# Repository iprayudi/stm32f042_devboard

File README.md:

# stm32f042_devboard

Use STM32CUBEIDE to run the example codes in this repository

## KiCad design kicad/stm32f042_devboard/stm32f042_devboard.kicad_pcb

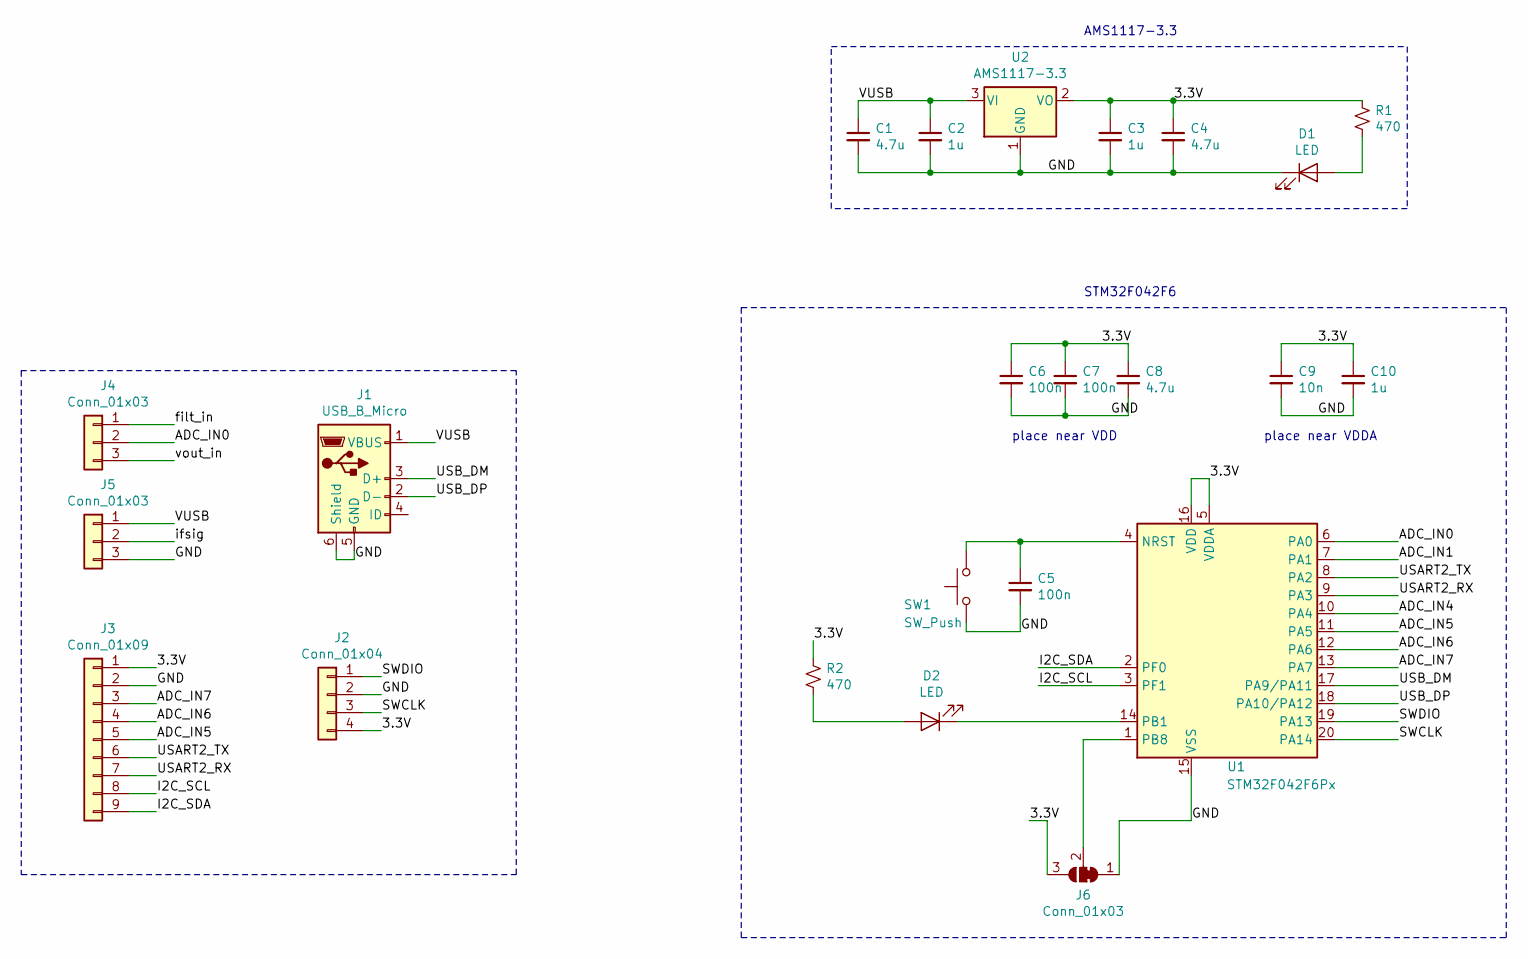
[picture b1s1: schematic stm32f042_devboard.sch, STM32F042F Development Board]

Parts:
C1, C4, C8: 4.7u; C_0805_2012Metric_Pad1.15x1.40mm_HandSolder; LCSC C1779
C2, C3, C10: 1u; C_0805_2012Metric_Pad1.15x1.40mm_HandSolder; LCSC C28323
C5, C6, C7: 100n; C_0805_2012Metric_Pad1.15x1.40mm_HandSolder; LCSC C49678
C9: 10n; C_0805_2012Metric_Pad1.15x1.40mm_HandSolder; LCSC C1710
D1, D2: LED; LED_0805_2012Metric_Pad1.15x1.40mm_HandSolder
J1: USB_B_Micro; USB_Micro-B_Amphenol_10103594-0001LF_Horizontal
J2: Conn_01x04; PinHeader_1x04_P2.54mm_Vertical
J3: Conn_01x09; PinHeader_1x09_P2.54mm_Vertical
J4, J5: Conn_01x03; PinHeader_1x03_P2.54mm_Vertical
J6: Conn_01x03; SolderJumper-3_P1.3mm_Bridged12_RoundedPad1.0x1.5mm
R1, R2: 470; R_0805_2012Metric_Pad1.15x1.40mm_HandSolder; LCSC C17710
SW1: SW_Push; SW_Push_1P1T_NO_CK_KSC6xxJ
U1: STM32F042F6Px; TSSOP-20_4.4x6.5mm_P0.65mm; LCSC C81000
U2: AMS1117-3.3; SOT-223-3_TabPin2; LCSC C6186

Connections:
/3.3V: C3.1, C4.1, C6.1, C7.1, C8.1, C9.1, C10.1, J2.4, J3.1, J6.3 (B), R1.1, R2.1, U1.5 (VDDA), U1.16 (VDD), U2.2 (VO)
/ADC_IN0: J4.2, U1.6 (PA0)
/ADC_IN1: U1.7 (PA1)
/ADC_IN4: U1.10 (PA4)
/ADC_IN5: J3.5, U1.11 (PA5)
/ADC_IN6: J3.4, U1.12 (PA6)
/ADC_IN7: J3.3, U1.13 (PA7)
/GND: C1.2, C2.2, C3.2, C4.2, C5.2, C6.2, C7.2, C8.2, C9.2, C10.2, D1.1 (K), J1.5 (GND), J1.6 (Shield), J2.2, J3.2, J5.3, J6.1 (A), SW1.1, U1.15 (VSS), U2.1 (GND)
/I2C_SCL: J3.8, U1.3 (PF1)
/I2C_SDA: J3.9, U1.2 (PF0)
/SWCLK: J2.3, U1.20 (PA14)
/SWDIO: J2.1, U1.19 (PA13)
/USART2_RX: J3.7, U1.9 (PA3)
/USART2_TX: J3.6, U1.8 (PA2)
/USB_DM: J1.3 (D+), U1.17 (PA9/PA11)
/USB_DP: J1.2 (D-), U1.18 (PA10/PA12)
/VUSB: C1.1, C2.1, J1.1 (VBUS), J5.1, U2.3 (VI)
/filt_in: J4.1
/ifsig: J5.2
/vout_in: J4.3
unnamed: C5.1, SW1.2, U1.4 (NRST)
unnamed: D1.2 (A), R1.2
unnamed: D2.1 (K), U1.14 (PB1)
unnamed: D2.2 (A), R2.2
unnamed: J6.2 (C), U1.1 (PB8)

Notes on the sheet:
place near VDDA
place near VDD
STM32F042F6
AMS1117-3.3

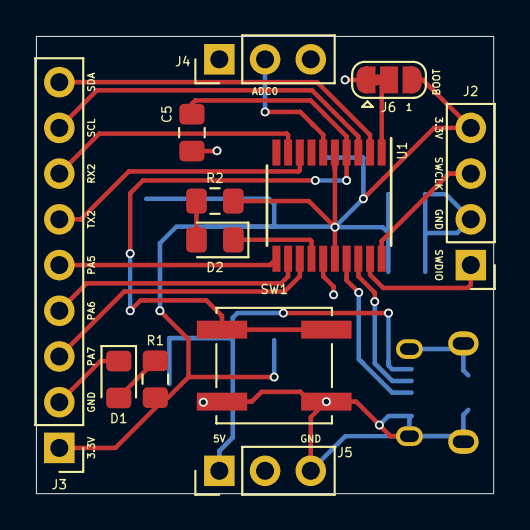
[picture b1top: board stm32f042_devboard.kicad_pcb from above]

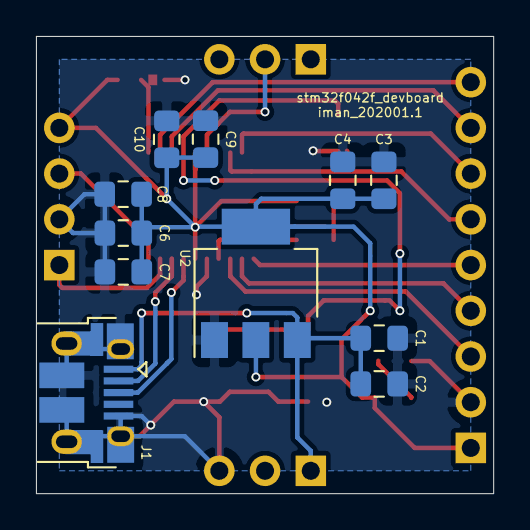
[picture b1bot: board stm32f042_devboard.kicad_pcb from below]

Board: 2 copper layers, 25.4 x 25.4 mm, 23 parts (11 on the bottom side), 20 nets.

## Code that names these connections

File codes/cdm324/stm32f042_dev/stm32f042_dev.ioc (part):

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Mcu.Name=STM32F042F6Px
Mcu.Package=TSSOP20
Mcu.UserName=STM32F042F6Px
PA0.Mode=IN0
PA0.Signal=ADC_IN0
PA11.Mode=Device
PA11.Signal=USB_DM
PA12.Mode=Device
PA12.Signal=USB_DP
PA2.Mode=Asynchronous
PA2.Signal=USART2_TX
PA3.Mode=Asynchronous
PA3.Signal=USART2_RX
PB1.GPIOParameters=GPIO_Label
PB1.GPIO_Label=LED
PB1.Signal=GPIO_Output
PF0-OSC_IN.Mode=I2C
PF0-OSC_IN.Signal=I2C1_SDA
PF1-OSC_OUT.Mode=I2C
PF1-OSC_OUT.Signal=I2C1_SCL
RCC.SYSCLKFreq_VALUE=48000000
RCC.SYSCLKSource=RCC_SYSCLKSOURCE_HSI48
board=custom

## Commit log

2020-01-18 added cdm324 project
2020-01-21 added example for fft transform (using Adafruit_ZeroFFT library)
2020-01-21 updated main.c
2020-01-21 removed cdm324 files
2020-01-28 added example codes - voltmeter
